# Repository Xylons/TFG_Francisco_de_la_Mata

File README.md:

# TFG_Francisco_de_la_Mata

Para ejecutar el insole-dashboard : ng serve

Para ejecutar el backend :  npm run start

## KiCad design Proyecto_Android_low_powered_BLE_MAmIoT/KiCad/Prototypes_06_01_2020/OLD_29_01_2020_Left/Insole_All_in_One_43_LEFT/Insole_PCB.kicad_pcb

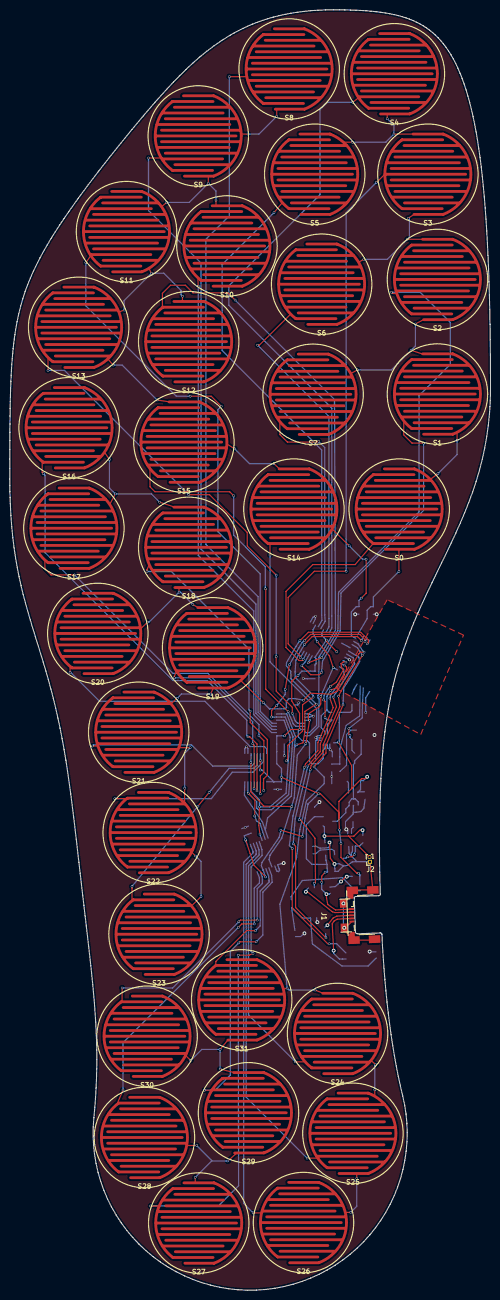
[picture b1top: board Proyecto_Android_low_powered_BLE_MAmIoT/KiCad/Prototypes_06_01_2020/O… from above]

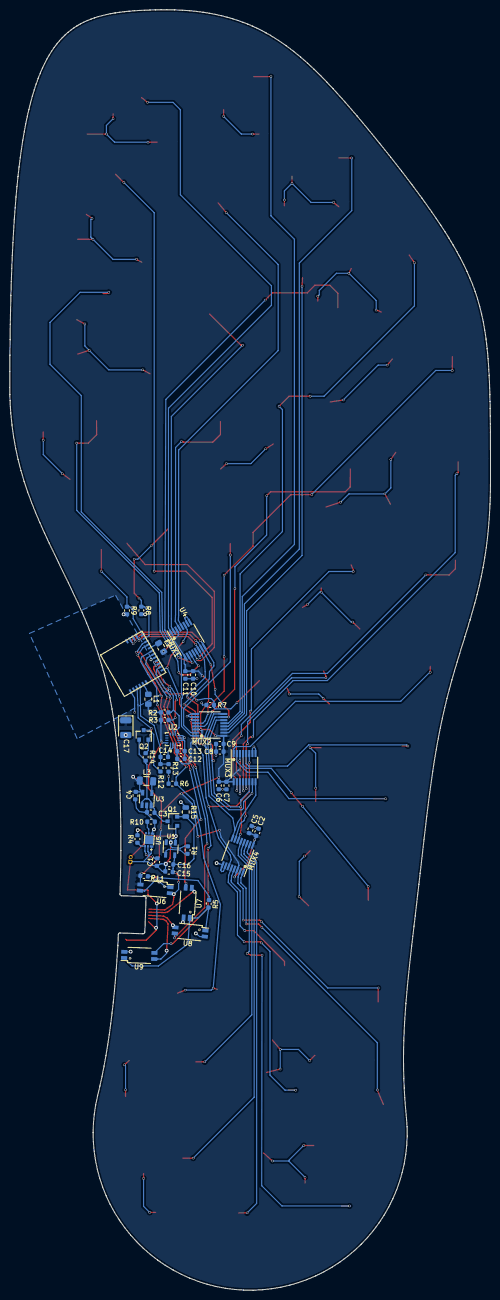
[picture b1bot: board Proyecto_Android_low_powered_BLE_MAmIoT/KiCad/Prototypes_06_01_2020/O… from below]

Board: 2 copper layers, 100.5 x 267.7 mm, 84 parts (50 on the bottom side), 66 nets.

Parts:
C1, C5, C7, C9, C11, C13, C14, C16: 0.1uF; C_0603_1608Metric
C2, C6, C8, C10, C12, C15: 1uF; C_0603_1608Metric
C3: 4.7uF; C_0603_1608Metric
C4: 10uF; C_0603_1608Metric
C17: 100uF; CP_EIA-3528-12_Kemet-T
J1: Conn_Micro_USB; USB_Micro_CustomV2
J2: 3V7_Battery; PinHeader_1x02_P1.00mm_Vertical
L1, L2: 300ohm 100MHz; L_0805_2012Metric_Pad1.15x1.40mm_HandSolder
L3: 1uH; L_1206_3216Metric
MUX1, MUX2, MUX3, MUX4: CD74HC4051; TSSOP-16_4.4x5mm_P0.65mm
Q1, Q2: Q_PMOS_GSD; SOT-23
R1, R2, R3, R6, R7, R8, R9, R12, R13: 10k; R_0603_1608Metric
R4: 390 ohm; R_0603_1608Metric
R5: 0-1k; R_0603_1608Metric
R10: 2.7k; R_0603_1608Metric
R11: 100-500 ohm; R_0603_1608Metric
R14: 100k; R_0603_1608Metric
R15: 10k; R_0805_2012Metric
S0, S1, S2, S3, S4, S5, S6, S7, S8, S9, S10, S11, S12, S13, S14, S15, S16, S17, S18, S19, S20, S21, S22, S23, S24, S25, S26, S27, S28, S29, S30, S31: FSR; FSR_Circle_9mm
U1: STC4054-4.2; TSOT-23-5
U2: ISM330DLC; Bosch_LGA-14_3x2.5mm_P0.5mm
U3: ADP2108AUJ-3.3; TSOT-23-5
U4: CYBLE-222014-01
U5: AP9211SA-AN-HAC-7; AP9211SAACHAC7
U6, U7, U8, U9: TCMT1100; SOP-4_4.4x2.8mm_P1.27mm

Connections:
+3V3: C2.2, C4.1, C5.2, C6.2, C7.2, C8.2, C9.2, C10.2, C11.2, C12.2, C13.2, C17.1, L1.1, L2.1, L3.2, MUX1.3, MUX1.16, MUX2.3, MUX2.16, MUX3.3, MUX3.16, MUX4.3, MUX4.16, R2.1, R3.1, R11.2, U2.5, U2.8, U3.4, U6.4
+5V: C15.2, C16.2, J1.1, Q1.1, R15.2, U1.4, U6.2
+BATT: J2.2, Q1.2, R4.1, U1.3
-BATT: C1.2, C15.1, C16.1, J1.5, J1.6, J2.1, R1.2, U1.2, U5.1, U5.2
/+3V3_VDD: L2.2, U4.14
/+3V3_VDDR: L1.2, U4.5
/+BATT_CUT: C3.2, Q1.3, Q2.2, R14.1, U3.1, U3.3
/MUX_E: MUX1.6, MUX2.6, MUX3.6, MUX4.6, U4.7
/P0.6_USB: J1.3, U8.4
/P0.7_USB: J1.4, U9.4
/S0: MUX1.11, MUX2.11, MUX3.11, MUX4.11, U4.19
/S1: MUX1.10, MUX2.10, MUX3.10, MUX4.10, U4.20
/S2: MUX1.9, MUX2.9, MUX3.9, MUX4.9, U4.21
/U1_A0: MUX1.13, S0.2
/U1_A1: MUX1.14, S1.2
/U1_A2: MUX1.15, S2.2
/U1_A3: MUX1.12, S3.2
/U1_A4: MUX1.1, S4.2
/U1_A5: MUX1.5, S5.2
/U1_A6: MUX1.2, S6.2
/U1_A7: MUX1.4, S7.2
/U1_Data: R9.2, S0.1, S1.1, S2.1, S3.1, S4.1, S5.1, S6.1, S7.1, U4.18
/U2_A0: MUX2.13, S8.2
/U2_A1: MUX2.14, S9.2
/U2_A2: MUX2.15, S10.2
/U2_A3: MUX2.12, S11.2
/U2_A4: MUX2.1, S12.2
/U2_A5: MUX2.5, S13.2
/U2_A6: MUX2.2, S14.2
/U2_A7: MUX2.4, S15.2
/U2_Data: R8.2, S8.1, S9.1, S10.1, S11.1, S12.1, S13.1, S14.1, S15.1, U4.17
/U3_A0: MUX3.13, S16.2
/U3_A1: MUX3.14, S17.2
/U3_A2: MUX3.15, S18.2
/U3_A3: MUX3.12, S19.2
/U3_A4: MUX3.1, S20.2
/U3_A5: MUX3.5, S21.2
/U3_A6: MUX3.2, S22.2
/U3_A7: MUX3.4, S23.2
/U3_Data: R7.2, S16.1, S17.1, S18.1, S19.1, S20.1, S21.1, S22.1, S23.1, U4.16
/U4_A0: MUX4.13, S24.2
/U4_A1: MUX4.14, S25.2
/U4_A2: MUX4.15, S26.2
/U4_A3: MUX4.12, S27.2
/U4_A4: MUX4.1, S28.2
/U4_A5: MUX4.5, S29.2
/U4_A6: MUX4.2, S30.2
/U4_A7: MUX4.4, S31.2
/U4_Data: R6.2, S24.1, S25.1, S26.1, S27.1, S28.1, S29.1, S30.1, S31.1, U4.13
/XRES_USB: J1.2, U7.4
Analog_Batt_Lvl: C14.1, R12.2, R13.1, U4.4
Enable_Batt_Lvl: Q2.1, R14.2, U4.3
GND: C2.1, C3.1, C4.2, C5.1, C6.1, C7.1, C8.1, C9.1, C10.1, C11.1, C12.1, C13.1, C14.2, C17.2, MUX1.7, MUX1.8, MUX2.7, MUX2.8, MUX3.7, MUX3.8, MUX4.7, MUX4.8, R6.1, R7.1, R8.1, R9.1, R10.2, R13.2, R15.1, U2.1, U2.2, U2.3, U2.6, U2.7, U3.2, U4.1, U4.11, U5.6, U7.2, U8.2, U9.2
unnamed: C1.1, R4.2, U5.3
unnamed: L3.1, U3.5
unnamed: Q2.3, R12.1
unnamed: R1.1, U1.5
unnamed: R2.2, U2.14, U4.9
unnamed: R3.2, U2.13, U4.10
unnamed: R5.1, U7.1, U8.1, U9.1
unnamed: R5.2, U6.3
unnamed: R10.1, U5.5
unnamed: R11.1, U6.1
P0.6: U4.12, U8.3
P0.7: U4.8, U9.3
XRES: U4.15, U7.3

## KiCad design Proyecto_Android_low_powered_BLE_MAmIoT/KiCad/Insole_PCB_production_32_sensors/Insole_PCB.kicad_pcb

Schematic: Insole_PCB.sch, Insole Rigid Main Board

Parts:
C1, C2: 1uF; C_0603_1608Metric_Pad1.05x0.95mm_HandSolder
C3: 4.7uF; C_0603_1608Metric_Pad1.05x0.95mm_HandSolder
C4: 10uF; C_0603_1608Metric_Pad1.05x0.95mm_HandSolder
J1: 5V_Qi; PinHeader_1x02_P1.00mm_Vertical
J2: 3V7_Battery; PinHeader_1x02_P1.00mm_Vertical
J3: SWD; PinHeader_1x04_P1.00mm_Vertical
J4: Conn_01x36_Male; Hirose_FH12-36S-0.5SH_1x36-1MP_P0.50mm_Horizontal
L1, L2: 300ohm 100MHz; L_0805_2012Metric_Pad1.15x1.40mm_HandSolder
L3: 1uH; L_0805_2012Metric_Pad1.15x1.40mm_HandSolder
R1, R2, R3, R4, R5, R6, R7: 10k; R_0603_1608Metric_Pad1.05x0.95mm_HandSolder
R9: 1M; R_0603_1608Metric_Pad1.05x0.95mm_HandSolder
R10: 200k; R_0603_1608Metric_Pad1.05x0.95mm_HandSolder
U1, U2, U3, U4: CD74HC4051; TSSOP-16_4.4x5mm_P0.65mm
U5: CYBLE-222014-01
U6: STC4054-4.2; TSOT-23-5
U7: ISM330DLC; Bosch_LGA-14_3x2.5mm_P0.5mm
U8: ADP2108AUJ-3.3; TSOT-23-5

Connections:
+3V3: C1.1, C4.1, L1.1, L2.1, L3.2, R2.1, R3.1, U1.3, U1.16, U2.3, U2.16, U3.3, U3.16, U4.3, U4.16, U7.5, U7.8, U8.4 (FB)
+5V: C2.2, J1.2, U6.4
+BATT: C3.2, J2.2, R9.2, U6.3, U8.1 (Vin), U8.3 (EN)
/MUX_E: U1.6, U2.6, U3.6, U4.6, U5.7
/S0: U1.11, U2.11, U3.11, U4.11, U5.19
/S1: U1.10, U2.10, U3.10, U4.10, U5.20
/S2: U1.9, U2.9, U3.9, U4.9, U5.21
/U1_A0: J4.8, U1.13
/U1_A1: J4.7, U1.14
/U1_A2: J4.6, U1.15
/U1_A3: J4.5, U1.12
/U1_A4: J4.4, U1.1
/U1_A5: J4.3, U1.5
/U1_A6: J4.2, U1.2
/U1_A7: J4.1, U1.4
/U1_Data: J4.17, R7.2, U5.18
/U2_A0: J4.16, U2.13
/U2_A1: J4.15, U2.14
/U2_A2: J4.14, U2.15
/U2_A3: J4.13, U2.12
/U2_A4: J4.12, U2.1
/U2_A5: J4.11, U2.5
/U2_A6: J4.10, U2.2
/U2_A7: J4.9, U2.4
/U2_Data: J4.18, R6.2, U5.17
/U3_A0: J4.28, U3.13
/U3_A1: J4.27, U3.14
/U3_A2: J4.26, U3.15
/U3_A3: J4.25, U3.12
/U3_A4: J4.24, U3.1
/U3_A5: J4.23, U3.5
/U3_A6: J4.22, U3.2
/U3_A7: J4.21, U3.4
/U3_Data: J4.19, R5.2, U5.16
/U4_A0: J4.36, U4.13
/U4_A1: J4.35, U4.14
/U4_A2: J4.34, U4.15
/U4_A3: J4.33, U4.12
/U4_A4: J4.32, U4.1
/U4_A5: J4.31, U4.5
/U4_A6: J4.30, U4.2
/U4_A7: J4.29, U4.4
/U4_Data: J4.20, R4.2, U5.13
GND: C1.2, C2.1, C3.1, C4.2, J1.1, J2.1, J3.1, R1.2, R4.1, R5.1, R6.1, R7.1, R10.1, U1.7, U1.8, U2.7, U2.8, U3.7, U3.8, U4.7, U4.8, U5.1, U5.11, U6.2, U7.1, U7.2, U7.3, U7.6, U7.7, U8.2 (GND)
unnamed: J3.2, U5.15
unnamed: J3.3, U5.8
unnamed: J3.4, U5.12
unnamed: L1.2, U5.5
unnamed: L2.2, U5.14
unnamed: L3.1, U8.5 (SW)
unnamed: R1.1, U6.5
unnamed: R2.2, U5.9, U7.14
unnamed: R3.2, U5.10, U7.13
unnamed: R9.1, R10.2, U5.22

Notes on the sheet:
Measure Battery level

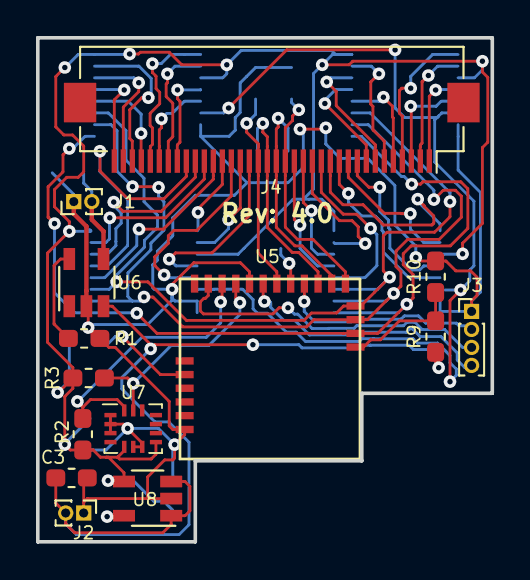
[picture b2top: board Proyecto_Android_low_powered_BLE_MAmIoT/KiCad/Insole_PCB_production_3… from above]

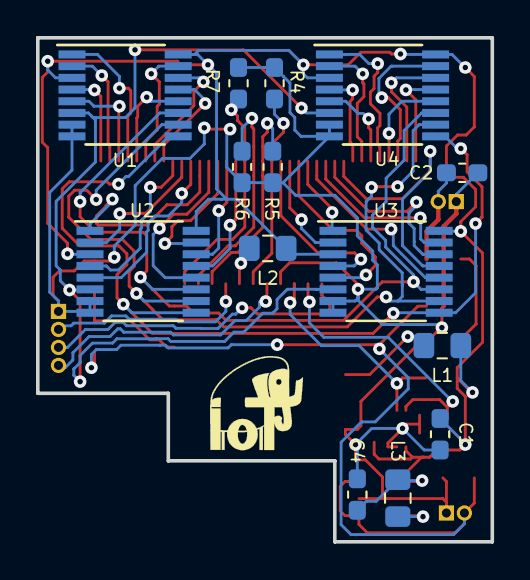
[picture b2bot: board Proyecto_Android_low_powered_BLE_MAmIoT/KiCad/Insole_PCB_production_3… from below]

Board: 2 copper layers, 25.2 x 28.0 mm, 28 parts (14 on the bottom side), 54 nets.

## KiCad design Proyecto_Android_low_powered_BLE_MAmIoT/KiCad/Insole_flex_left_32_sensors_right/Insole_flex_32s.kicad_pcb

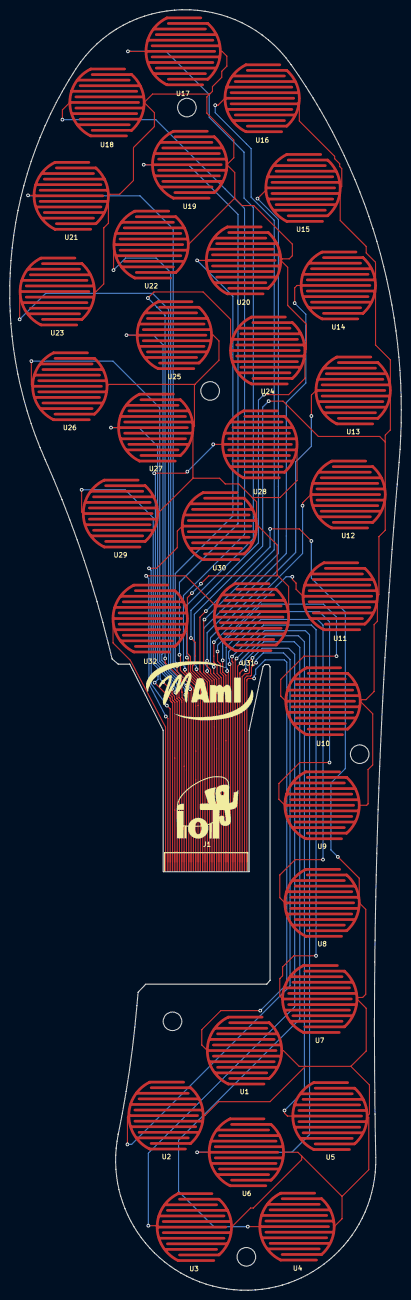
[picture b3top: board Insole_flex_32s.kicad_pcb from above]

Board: 2 copper layers, 84.3 x 275.6 mm, 33 parts (0 on the bottom side), 36 nets.

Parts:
J1: Conn_01x36_Male; fpc_female_36_pitch_0.5mm
U1, U2, U3, U4, U5, U6, U7, U8, U9, U10, U11, U12, U13, U14, U15, U16, U17, U18, U19, U20, U21, U22, U23, U24, U25, U26, U27, U28, U29, U30, U31, U32: FSR; FSR_Circle_8mm

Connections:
unnamed: J1.1, U1.2
unnamed: J1.2, U2.2
unnamed: J1.3, U3.2
unnamed: J1.4, U4.2
unnamed: J1.5, U5.2
unnamed: J1.6, U6.2
unnamed: J1.7, U7.2
unnamed: J1.8, U8.2
unnamed: J1.9, U9.2
unnamed: J1.10, U10.2
unnamed: J1.11, U11.2
unnamed: J1.12, U12.2
unnamed: J1.13, U13.2
unnamed: J1.14, U14.2
unnamed: J1.15, U15.2
unnamed: J1.16, U16.2
unnamed: J1.17, U1.1, U2.1, U3.1, U4.1, U5.1, U6.1, U7.1, U8.1
unnamed: J1.18, U9.1, U10.1, U11.1, U12.1, U13.1, U14.1, U15.1, U16.1
unnamed: J1.19, U17.1, U18.1, U19.1, U20.1, U21.1, U22.1, U23.1, U24.1
unnamed: J1.20, U25.1, U26.1, U27.1, U28.1, U29.1, U30.1, U31.1, U32.1
unnamed: J1.21, U17.2
unnamed: J1.22, U18.2
unnamed: J1.23, U19.2
unnamed: J1.24, U20.2
unnamed: J1.25, U21.2
unnamed: J1.26, U22.2
unnamed: J1.27, U23.2
unnamed: J1.28, U24.2
unnamed: J1.29, U25.2
unnamed: J1.30, U26.2
unnamed: J1.31, U27.2
unnamed: J1.32, U28.2
unnamed: J1.33, U29.2
unnamed: J1.34, U30.2
unnamed: J1.35, U31.2
unnamed: J1.36, U32.2

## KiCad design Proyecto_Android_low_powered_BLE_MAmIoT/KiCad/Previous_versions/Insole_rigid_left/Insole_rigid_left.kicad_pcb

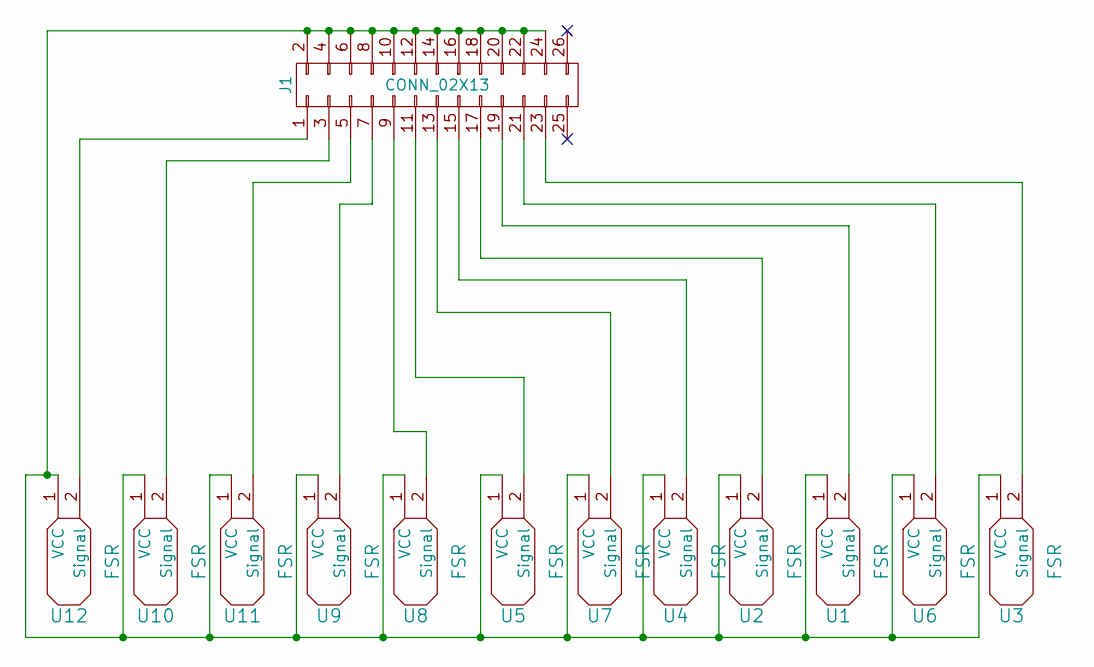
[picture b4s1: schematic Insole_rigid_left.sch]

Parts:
J1: CONN_02X13; Socket_Strip_Straight_2x13_Pitch1.27mm_SMD
U1, U2, U3, U4, U5, U6, U7, U8, U9, U10, U11, U12: FSR; FSR15x30mm

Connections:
unnamed: J1.1, U12.2 (Signal)
unnamed: J1.3, U10.2 (Signal)
unnamed: J1.5, U11.2 (Signal)
unnamed: J1.7, U9.2 (Signal)
unnamed: J1.9, U8.2 (Signal)
unnamed: J1.2, J1.4, J1.6, J1.8, J1.10, J1.12, J1.14, J1.16, J1.18, J1.20, J1.22, J1.24, U1.1 (VCC), U2.1 (VCC), U3.1 (VCC), U4.1 (VCC), U5.1 (VCC), U6.1 (VCC), U7.1 (VCC), U8.1 (VCC), U9.1 (VCC), U10.1 (VCC), U11.1 (VCC), U12.1 (VCC)
unnamed: J1.11, U5.2 (Signal)
unnamed: J1.13, U7.2 (Signal)
unnamed: J1.15, U4.2 (Signal)
unnamed: J1.17, U2.2 (Signal)
unnamed: J1.19, U1.2 (Signal)
unnamed: J1.21, U6.2 (Signal)
unnamed: J1.23, U3.2 (Signal)

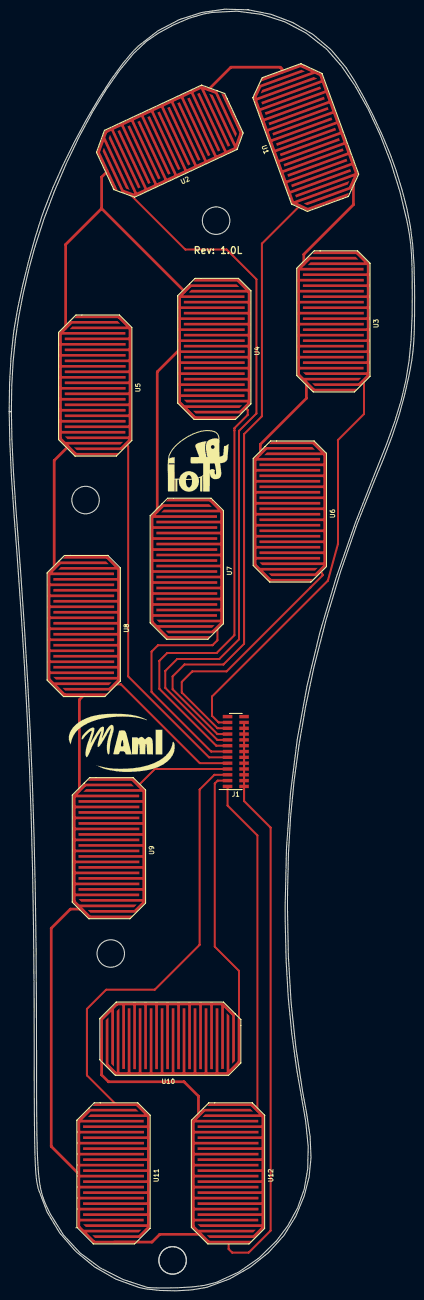
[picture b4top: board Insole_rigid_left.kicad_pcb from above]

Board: 2 copper layers, 88.5 x 279.8 mm, 13 parts (0 on the bottom side), 13 nets.

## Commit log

2020-03-21 Comienzo de la estructura de web Angular con sus dependencias
2020-03-25 limpieza
2020-03-25 Creada la estructura basica, angular, node js con express y mongodb en localhost
2020-03-28 version with template driven approach
2020-04-01 Anadido funcion de borrar editar y anadir fotos siguiendo reactive approach
2020-04-01 pagination added
2020-04-08 anadido autenticacion y autorizacion
2020-04-10 anadido control de errores y modularidad
2020-04-11 formada la base del proyecto con optimizaciones de codigo
2020-04-15 anadida barra de navegacion responsive, lateral
2020-04-17 anadida página con cards
2020-05-06 Anadido ng-charjs
2020-05-12 anadido controles con distintos roles
2020-05-16 anadido reset de contraseña
2020-05-26 anadido snackbar en recuperacion de password
2020-05-31 anadido perfiles usuarios back
2020-06-04 anadido perfil basico, a falta de anadir los perfiles especiales
2020-06-22 anadidas las funcionalidades de los roles, edicion de perfiles,api pernalizada para extraer usuarios segun tipo y administracion
2020-06-23 solucion de errores en perfiles, anadido componente dialog y snackbar para mostrar feedback
2020-06-23 arreglado estilo de dialog
2020-06-24 ACTUALIZADAS LIBRERIAS y problemas de versiones
2020-06-26 mejorado diseño de la web y cambiado el diseño de profile-list
2020-07-01 version inicial de barra de busqueda
2020-07-03 anadidos valores de busqueda en back y se barra de busqueda flotante
2020-07-06 los fitros de busqueda se extraen personalizados y anadida funcionalidad de anadir paciente a responsable
2020-07-11 anadidos elementos en dashboard, sentencias de back que sirven a dashboard y lectura de ficheros csv
2020-07-12 anadidos botones para seleccionar rangos de fechas
2020-07-13 anadida api para recepcion de datos y decodificacion, y anadidos label para graficar la info individual en dashboard
2020-07-15 anadido servicio para almacenar informacion a la aplicacion android, en proceso anadir comparativa de pacientes en dashboard
2020-07-16 modificados los tipos de Documents para almacenar plantilla por hora y por dia
2020-07-16 modificadas las llamadas de dashbard en back y front
2020-07-16 terminada graficacion en modo comparativa
2020-07-21 cambios esteticos y actualizados campos de perfil de paciente
2020-07-26 anadido logo y cambios de diseño
2020-07-27 cambios de nombre
2020-07-27 anadida vista de dashboard
2020-09-02 Subidos cambios previos, y preparación para hacer publico el repositorio
2020-09-03 optimizacion de compare
2020-09-03 correcion
2020-09-22 Anadidos datos de la bd
2020-09-22 Bump bcrypt from 4.0.1 to 5.0.0 in /backend
    Bumps [bcrypt](https://github.com/kelektiv/node.bcrypt.js) from 4.0.1 to 5.0.0.
    - [Release notes](https://github.com/kelektiv/node.bcrypt.js/releases)
    - [Changelog](https://github.com/kelektiv/node.bcrypt.js/blob/master/CHANGELOG.md)
    - [Commits](https://github.com/kelektiv/node.bcrypt.js/compare/v4.0.1...v5.0.0)
2020-09-22 Bump node-fetch from 2.6.0 to 2.6.1 in /backend
    Bumps [node-fetch](https://github.com/bitinn/node-fetch) from 2.6.0 to 2.6.1.
    - [Release notes](https://github.com/bitinn/node-fetch/releases)
    - [Changelog](https://github.com/node-fetch/node-fetch/blob/master/docs/CHANGELOG.md)
    - [Commits](https://github.com/bitinn/node-fetch/compare/v2.6.0...v2.6.1)
2020-09-22 Bump bl from 2.2.0 to 2.2.1 in /backend
    Bumps [bl](https://github.com/rvagg/bl) from 2.2.0 to 2.2.1.
    - [Release notes](https://github.com/rvagg/bl/releases)
    - [Commits](https://github.com/rvagg/bl/compare/v2.2.0...v2.2.1)
2020-12-08 Bump fast-csv from 4.3.1 to 4.3.6 in /backend
    Bumps [fast-csv](https://github.com/C2FO/fast-csv/tree/HEAD/packages/fast-csv) from 4.3.1 to 4.3.6.
    - [Release notes](https://github.com/C2FO/fast-csv/releases)
    - [Changelog](https://github.com/C2FO/fast-csv/blob/master/packages/fast-csv/CHANGELOG.md)
    - [Commits](https://github.com/C2FO/fast-csv/commits/v4.3.6/packages/fast-csv)
2020-12-13 Bump ini from 1.3.5 to 1.3.8 in /backend
    Bumps [ini](https://github.com/isaacs/ini) from 1.3.5 to 1.3.8.
    - [Release notes](https://github.com/isaacs/ini/releases)
    - [Commits](https://github.com/isaacs/ini/compare/v1.3.5...v1.3.8)
2021-05-12 Bump nodemailer from 6.4.6 to 6.4.16 in /backend
    Bumps [nodemailer](https://github.com/nodemailer/nodemailer) from 6.4.6 to 6.4.16.
    - [Release notes](https://github.com/nodemailer/nodemailer/releases)
    - [Changelog](https://github.com/nodemailer/nodemailer/blob/master/CHANGELOG.md)
    - [Commits](https://github.com/nodemailer/nodemailer/compare/v6.4.6...v6.4.16)
2021-06-12 Bump glob-parent from 5.1.1 to 5.1.2 in /backend
    Bumps [glob-parent](https://github.com/gulpjs/glob-parent) from 5.1.1 to 5.1.2.
    - [Release notes](https://github.com/gulpjs/glob-parent/releases)
    - [Changelog](https://github.com/gulpjs/glob-parent/blob/main/CHANGELOG.md)
    - [Commits](https://github.com/gulpjs/glob-parent/compare/v5.1.1...v5.1.2)
    ---
    updated-dependencies:
